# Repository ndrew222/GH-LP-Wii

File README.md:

# Guitar Hero Les Paul Wii PCB (Currently WIP)

This repo contains files for my prototype to create a PCB for the Wii Les Paul guitar.
The design will aim to utilise at most 2 layers, without the need for vias, so that I can use the school's PCB maker.

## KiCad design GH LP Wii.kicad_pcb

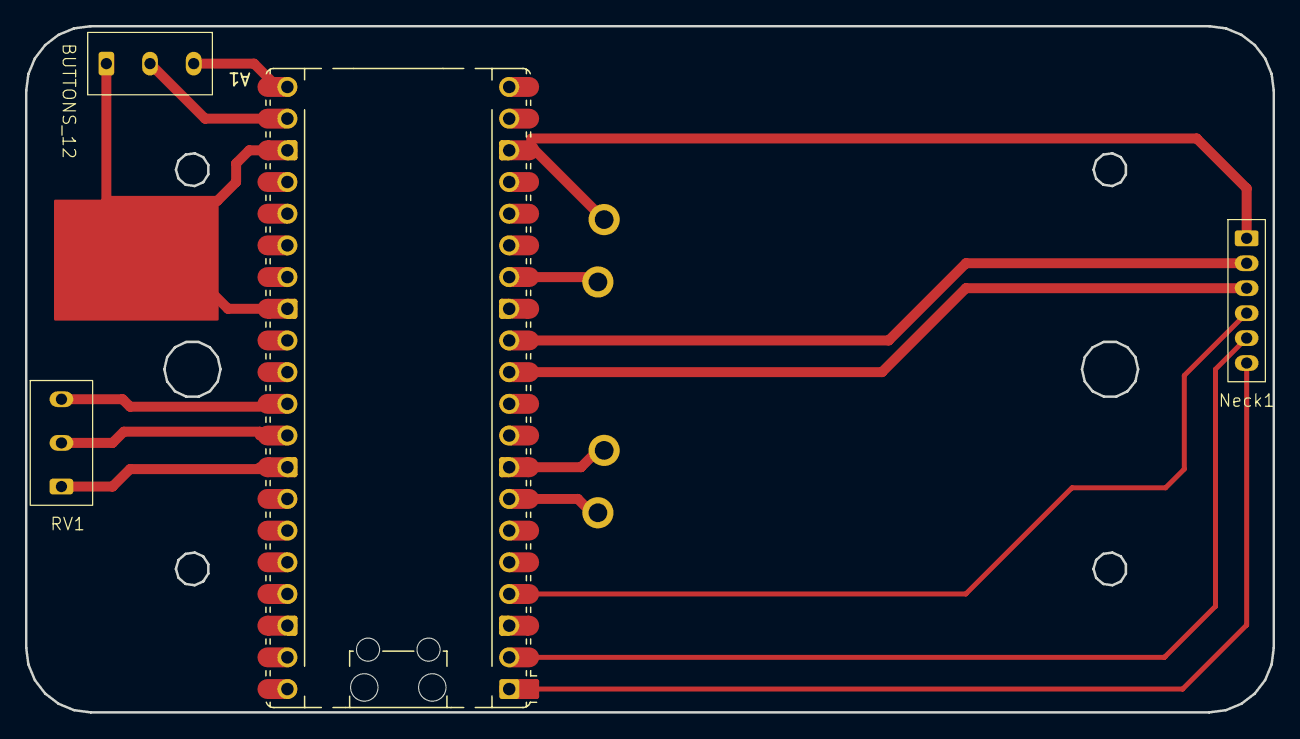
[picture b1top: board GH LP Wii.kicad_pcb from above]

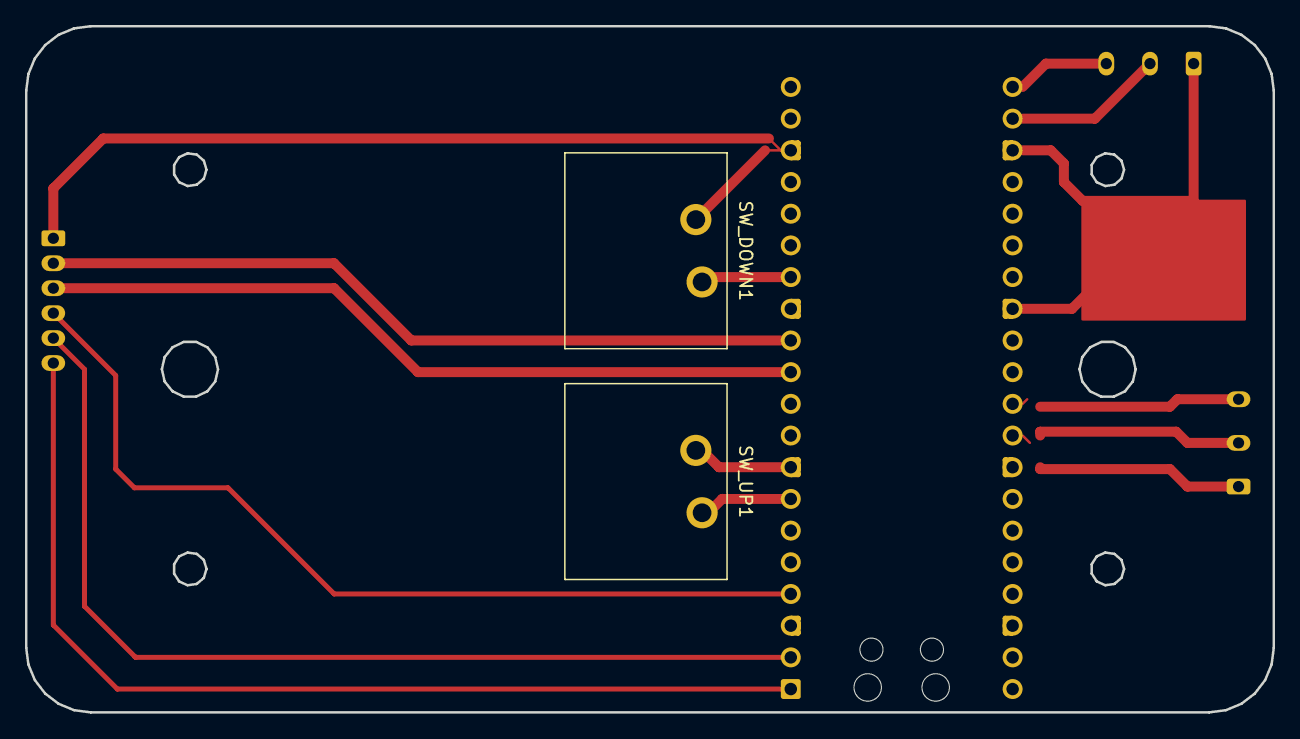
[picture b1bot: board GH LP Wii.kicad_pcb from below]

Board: 2 copper layers, 100.0 x 55.0 mm, 6 parts (2 on the bottom side), 13 nets.

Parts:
A1: RaspberryPi_Pico; RaspberryPi_Pico_Common_Unspecified
BUTTONS_12: Whammy Pot
Neck1: Frets
RV1: R_Potentiometer; Whammy Pot
SW_DOWN1: SW_Push_45deg; SW_Alps_Matias
SW_UP1: SW_Push_45deg; SW_Alps_Matias

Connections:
unnamed: A1.33 (AGND), RV1.3
unnamed: A1.1 (GPIO0), Neck1.1 (Green)
unnamed: A1.2 (GPIO1), Neck1.2 (Red)
unnamed: A1.4 (GPIO2), Neck1.3 (Yellow)
unnamed: A1.7 (GPIO5), SW_UP1.2
unnamed: A1.11 (GPIO8), Neck1.4 (Blue)
unnamed: A1.12 (GPIO9), Neck1.5 (Orange)
unnamed: A1.14 (GPIO10), SW_DOWN1.2
unnamed: A1.21 (GPIO16), BUTTONS_12.1
unnamed: A1.22 (GPIO17), BUTTONS_12.2
unnamed: A1.31 (GPIO26_ADC0), RV1.1
unnamed: A1.32 (GPIO27_ADC1), RV1.2
unnamed: A1.3 (GND), A1.8 (GND), A1.13 (GND), A1.18 (GND), A1.23 (GND), A1.28 (GND), A1.38 (GND), BUTTONS_12.3, Neck1.6 (GND), SW_DOWN1.1, SW_UP1.1

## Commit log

2025-08-28 add strumbar stl
2025-08-28 create gitignore
2025-08-28 add README
2025-09-09 add strumbar dxf
2025-09-09 uhh mostly done I guess
2025-09-09 add edge cuts
2025-09-09 gonna print
2025-10-19 Update settings and stuff
